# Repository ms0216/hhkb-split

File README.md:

# hhkb-split

**HHKB Professional HYBRID Type-S（PD-KB800WNS / US配列 / 無刻印）の使い勝手を、
完全分割型で再現する自作キーボード。**

> **開発中です。** 実機での動作確認はまだ済んでいません。
> 現状は「CAD とファームウェアがビルドを通り、寸法と配列が実機調査で裏付けられている」段階です。
> 3Dプリント・基板発注・組み立ては未実施。

## 基本方針

**HHKB オリジナルの使い勝手を極力踏襲する。** 分割にするために必要な変更だけを加え、
それ以外は変えない。この方針は [tools/test_invariants.py](tools/test_invariants.py) に
テストとして書き下してあり、設計の都合で妥協しようとすると機械的に落ちる。

守っているもの:

| 項目 | 値 | 根拠 |
|---|---|---|
| キーピッチ | 19.05mm | 実機公称 |
| 打鍵面の傾斜 | 7.3° | 実機ノギス実測 |
| 手前端の高さ | 17.5mm | 実測 17mm と別レビュー約18mm の中間 |
| キートップ高さ（各段） | 26.7 / 29.2 / 31.6 / 35.6 / 40.0mm | 公称全高 40mm から導出 |
| チルト脚 | 0 / 3 / 6° の3段階 | 実機と同一 |
| 行ずれ | HHKB と同一（格子配列にしない） | 実機 |
| 最下段 | 外側 1u / スペース寄り 1.5u | QMK info.json + KLE 図 |
| 電源 | 単3 × 2 | 実機と同じ思想（リポにしない） |

変更したもの:

- **打鍵感** — 静電容量無接点（Topre）→ MX 互換 + ホットスワップソケット
- **分割** — 6u スペースを 3u + 3u に分割。**左右とも Space**。キーは増やさない（60 → 61）
- **Mac/Win 切替** — 実機の DIP スイッチ相当をソフトウェアで実現
- **無線** — 左右間も Bluetooth。TRRS 有線は障害時の予備でしかない

## 構成

```
layout/        HHKB オリジナルと分割版のキー配列（JSON）
tools/         配列読み込み・CAD生成・検証（Python / build123d）
config/        ZMK ファームウェア設定
docs/hardware/ 実機の寸法調査と、その出典・失敗した調査経路の記録
build/         生成された STL（未印刷）
```

### tools/

パラメトリック CAD。`build123d`（OCCT）でモデルを生成し、`trimesh` で
メッシュ健全性を、OrcaSlicer CLI で実際にスライスできるかを検証する。

```bash
python -m pytest tools          # 全検査（約 14 分。件数は --collect-only で数える）
python tools/gen_case.py        # ケースを生成
python tools/verify.py          # メッシュとスライスの検証
```

[tools/interface.py](tools/interface.py) は**プレート・ケース・基板が共有する境界**を
1 箇所に集めたもの。ケースは刷り直せるが基板は発注し直すと高くつくので、
ここを凍結してから発注する。

### config/

ZMK。ボードは **Seeed Studio XIAO nRF52840**（技適 211-220207）。
XIAO は GPIO が 11 本しかなく普通のマトリクスに 1 本足りないため、列の駆動に
シフトレジスタ **SN74LVC595APWR** を使う（ZMK 公式が推奨する手段）。**74HC595 では打ち止め時に規格外**（動作電圧の下限 2.0V に対し、レールは 1.8V まで下がる）と分かって差し替えた。キーごとにダイオード 1 個の
ごく普通の行×列マトリクスなので、同時押しでゴーストが出ない。
当初はチャープレックス方式で設計していたが、基板発注前に破棄した
（[判断根拠](docs/hardware/decisions/2026-08-07-keyscan.md)）。

| シールド | 用途 |
|---|---|
| `hhkb_split_left` / `hhkb_split_right` | 本番。4レイヤー × 61キー |
| `proto_direct` | 疎通確認（XIAO 1個・キー2個）（[手順書](docs/hardware/task-c1-smoke-test.md)）✅ 実機確認済 |
| `proto_matrix` | マトリクス配線とゴースト試験の治具（[手順書](docs/hardware/task-c2-keyscan.md)）✅ 実機確認済 |

ビルドは GitHub Actions（ZMK 公式の再利用ワークフロー）。Actions の成果物から
`.uf2` をダウンロードして書き込む。

### 検証タスクの手順書

実機で確かめる作業は、配置図と判定基準つきの手順書にしてある。

| タスク | 内容 | 状態 |
|---|---|---|
| [C1](docs/hardware/task-c1-smoke-test.md) | 疎通確認（XIAO・書き込み・ZMK が実機で動くか） | ✅ 合格 |
| [C2](docs/hardware/task-c2-keyscan.md) | キースキャン（マトリクス・ゴースト・シフトレジスタ。治具は 74HC595、本番は 74LVC595） | ✅ C2-a 合格 / ⬜ C2-b |
| [C3](docs/hardware/task-c3-ble-split.md) | BLE 分割（左右同時押しが崩れないか） | ⬜ |
| [C4・C5](docs/hardware/task-c4-c5-power.md) | 乾電池給電・逆流の測定・電池残量 | ⬜ |
| [C6](docs/hardware/task-c6-confirm-on-real-hhkb.md) | 実機の DIP スイッチとキーマップを確認 | ⬜ **部品不要** |
| [B3](docs/hardware/task-b3-print-and-compare.md) | 3Dプリントして実機と比べる | ⬜ **部品不要** |

書き込みでつまずいたときは [xiao-flash-recovery.md](docs/hardware/xiao-flash-recovery.md)。

### docs/hardware/

実機を分解せず、公開情報だけから寸法を確定させた記録。
[reference-sources.md](docs/hardware/reference-sources.md) には**失敗した調査経路 11 件**も
残してある（例: PFU 公式記事に載っていた側面写真 4 枚が、よく見ると HHKB ではなく
MX 軸のキーボードだった）。同じ穴に落ちないため。

## 進捗

| フェーズ | 状態 |
|---|---|
| A. 実機寸法の確定 | ✅ 完了 |
| B. 機構設計（プレート・ケース） | ✅ STL 生成・検証済み / ⬜ 未印刷（[B3](docs/hardware/task-b3-print-and-compare.md)） |
| C. 電気・ファームウェア検証 | 🔶 進行中（**C1・C2-a 合格**。C2-b は 74HC595（治具用。本番は 74LVC595）待ち、C3〜C5 は部品待ち） |
| D. 基板設計（KiCad → JLCPCB） | 🔶 D1・D2a 完了（外形・キー配置・マトリクス）。[詳細](pcb/README.md) |
| E. 組み立て・実機調整 | ⬜ 未着手 |

## ライセンス

未定。

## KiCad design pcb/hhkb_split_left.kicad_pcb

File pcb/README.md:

# 基板（KiCad）

## 現在の状態

| 段階 | 内容 | 状態 |
|---|---|---|
| D1 | 外形・キー配置・取付穴 | ✅ 完了。DRC 違反 0 |
| D2a | マトリクス（61キー ＋ 61ダイオード ＋ 行列のネット） | ✅ 完了 |
| D3a | マトリクスの配線（行・列・スイッチ→ダイオード） | ✅ 左は違反 0 / ⚠️ 右に 5 件（下記） |
| D2b | XIAO・74HC595・電源の搭載 | ⬜ 3D 実装の検討が要る（下記） |
| D3 | 配線（行・列・電源） | ⬜ |
| D4 | JLCPCB 向け出力（ガーバー・BOM・CPL） | ⬜ |

マトリクスは配線済み（**未配線 0**）。左半分は DRC 違反 0。

### 右半分に残る 5 件

すべて `hole_clearance`（配線が穴に近すぎる）で、原因は特定済み。

列のバスは行間の空きを横に渡るが、**スタビライザーの穴がその帯に食い込んで
いる**（キー中心 +6.2〜10.2mm）。9 列ぶんの通り道を 0.8mm 間隔で並べると、
穴を避けきれない列が出る。

取りうる手:
  1. 穴に当たる区間だけ迂回させる（自動配線の作り込み）
  2. 配線幅と間隔を詰めて通り道を増やす（JLCPCB の最小は 0.127mm）
  3. 該当箇所だけ KiCad の GUI で手直しする

**左半分が完全に通っているので、方式の問題ではない。**

### D2b でまず決めること — XIAO をどこに置くか

XIAO は基板の**裏面**に付く（表に置くとキーキャップと当たる）。ところが
USB-C は実機と同じく**背面**に出す必要があり、基板の裏の背面側には
**電池室（幅 109mm）**が横断している。左半分では電池の外側に
15mm ほどしか残らず、XIAO の 17.8mm が入らない。

取りうる案:
  1. USB-C を基板端のコネクタとして別に載せ、XIAO は空いている隅に置く
  2. 電池を左右に振り分けて中央を空ける（ケースの作り直しが要る）
  3. USB の位置を実機と変える（使い勝手の方針に反するので最後）

**ケースの 3D モデルと合わせて検討する必要がある。** 実測（Task C4）で
電源部の構成が確定してから着手するのが順序として正しい。

## 生成のしかた

`pcbnew` は KiCad 同梱の Python にしか無いので、そちらで動かす。

```bash
/Applications/KiCad/KiCad.app/Contents/Frameworks/Python.framework/Versions/3.9/bin/python3.9 \
    tools/gen_pcb.py
```

## 検証のしかた

```bash
# デザインルール検査（違反があれば終了コードが非 0）
/Applications/KiCad/KiCad.app/Contents/MacOS/kicad-cli pcb drc \
    --severity-error --exit-code-violations pcb/hhkb_split_left.kicad_pcb

# 生成物が設計値と一致するか（通常の pytest から実行できる）
python -m pytest tools/test_pcb.py

# 目で見る
/Applications/KiCad/KiCad.app/Contents/MacOS/kicad-cli pcb render \
    --output /tmp/pcb.png --side top pcb/hhkb_split_left.kicad_pcb
```

`.kicad_pcb` はテキスト（S 式）なので、`tools/test_pcb.py` は pcbnew 無しで
読める。**生成した基板を読み返して、プレート・ケースと突き合わせる**のが要点。
別々に生成される以上、同じ設計値から導いていても座標変換を間違えれば静かに
ずれる。ずれたまま発注すると数万円が無駄になる。

## 寸法

| | 左 | 右 |
|---|---|---|
| 基板 | 140.36 × 102.00mm | 173.70 × 102.00mm |
| スイッチ | 27 | 34 |
| スタビライザー | 2 | 2 |
| 取付穴 | 7 | 7 |

外形はプレートより片側 3.0mm 小さい（`interface.PCB_INSET`）。ケースの
側壁 2.4mm の内側に収める必要があるため。

奥行 102.00mm ＝ プレート 108.00mm − 6.0mm。プレートの 108.00mm は
HHKB 実機の本体奥行そのもの。

## ライブラリ

`lib/` を参照。KiCad 標準に無い 3.00u とホットスワップソケットだけを
kiswitch から取り込み、寸法を規格値と照合してある。

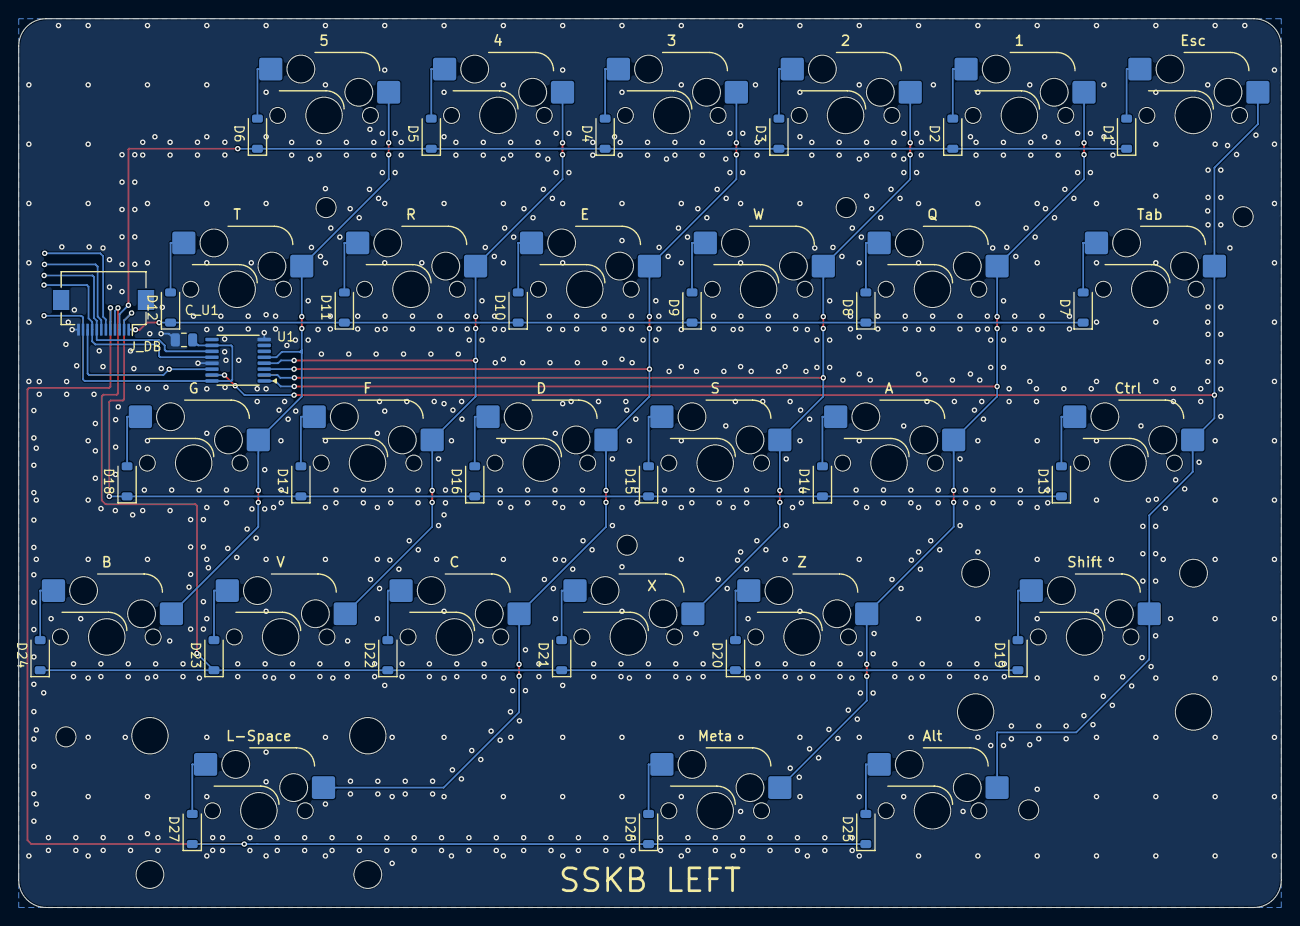
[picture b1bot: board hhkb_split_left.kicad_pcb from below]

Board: 2 copper layers, 138.4 x 97.4 mm, 65 parts (30 on the bottom side), 43 nets.

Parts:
C_U1: 100nF; C_0805_2012Metric
D1, D2, D3, D4, D5, D6, D7, D8, D9, D10, D11, D12, D13, D14, D15, D16, D17, D18, D19, D20, D21, D22, D23, D24, D25, D26, D27: BAT46W; D_SOD-123
H0, H1, H2, H3, H4, H5: MountingHole_2.2mm_M2
J_DB: FH12-12S-0.5SH(55); Hirose_FH12-12S-0.5SH_1x12-1MP_P0.50mm_Horizontal
ST19, ST27: Stabilizer_Cherry_MX_2.00u
SW1, SW2, SW3, SW4, SW5, SW6, SW8, SW9, SW10, SW11, SW12, SW14, SW15, SW16, SW17, SW18, SW20, SW21, SW22, SW23, SW24, SW25: CPG151101S11-2; SW_Hotswap_Kailh_MX_1.00u
SW7, SW26: CPG151101S11-2; SW_Hotswap_Kailh_MX_1.50u
SW13: CPG151101S11-2; SW_Hotswap_Kailh_MX_1.75u
SW19: CPG151101S11-2; SW_Hotswap_Kailh_MX_2.25u
SW27: CPG151101S11-2; SW_Hotswap_Kailh_MX_2.75u
U1: 74LVC595; TSSOP-16_4.4x5mm_P0.65mm

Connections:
COL0: SW1.1, SW7.1, SW13.1, SW19.1, SW25.1, U1.15
COL1: SW2.1, SW8.1, SW14.1, SW20.1, SW26.1, U1.1
COL2: SW3.1, SW9.1, SW15.1, SW21.1, U1.2
COL3: SW4.1, SW10.1, SW16.1, SW22.1, SW27.1, U1.3
COL4: SW5.1, SW11.1, SW17.1, SW23.1, U1.4
COL5: SW6.1, SW12.1, SW18.1, SW24.1, U1.5
CS: J_DB.9, U1.12
GND: C_U1.2, J_DB.12, U1.8, U1.13
ROW_A: D25.1, D26.1, D27.1, J_DB.5
ROW_B: D19.1, D20.1, D21.1, D22.1, D23.1, D24.1, J_DB.4
ROW_C: D1.1, D2.1, D3.1, D4.1, D5.1, D6.1, J_DB.3
ROW_D: D13.1, D14.1, D15.1, D16.1, D17.1, D18.1, J_DB.2
ROW_E: D7.1, D8.1, D9.1, D10.1, D11.1, D12.1, J_DB.1
SPI_MOSI: J_DB.10, U1.14
SPI_SCK: J_DB.8, U1.11
SW1_D: D1.2, SW1.2
SW2_D: D2.2, SW2.2
SW3_D: D3.2, SW3.2
SW4_D: D4.2, SW4.2
SW5_D: D5.2, SW5.2
SW6_D: D6.2, SW6.2
SW7_D: D7.2, SW7.2
SW8_D: D8.2, SW8.2
SW9_D: D9.2, SW9.2
SW10_D: D10.2, SW10.2
SW11_D: D11.2, SW11.2
SW12_D: D12.2, SW12.2
SW13_D: D13.2, SW13.2
SW14_D: D14.2, SW14.2
SW15_D: D15.2, SW15.2
SW16_D: D16.2, SW16.2
SW17_D: D17.2, SW17.2
SW18_D: D18.2, SW18.2
SW19_D: D19.2, SW19.2
SW20_D: D20.2, SW20.2
SW21_D: D21.2, SW21.2
SW22_D: D22.2, SW22.2
SW23_D: D23.2, SW23.2
SW24_D: D24.2, SW24.2
SW25_D: D25.2, SW25.2
SW26_D: D26.2, SW26.2
SW27_D: D27.2, SW27.2
V3V3: C_U1.1, J_DB.11, U1.10, U1.16

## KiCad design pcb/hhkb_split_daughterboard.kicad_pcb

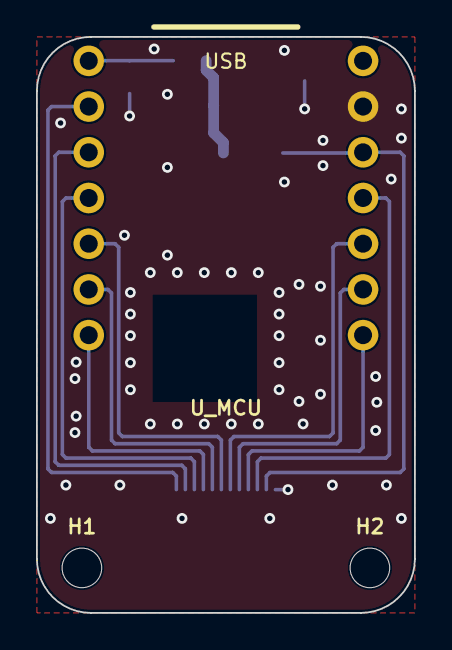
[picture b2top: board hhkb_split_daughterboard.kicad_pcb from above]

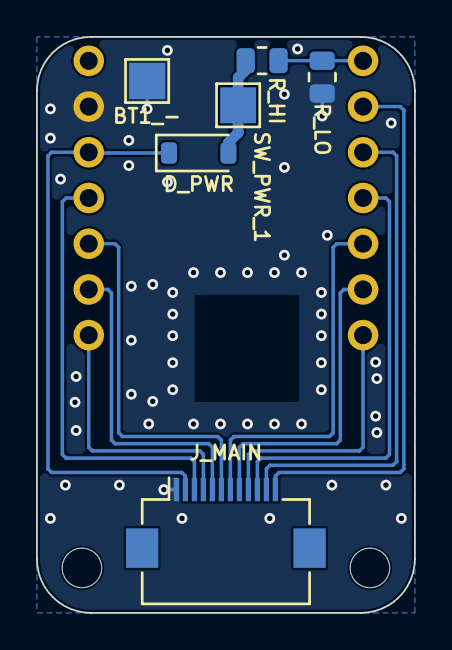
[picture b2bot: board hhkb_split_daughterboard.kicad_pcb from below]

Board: 2 copper layers, 21.0 x 32.0 mm, 9 parts (6 on the bottom side), 14 nets.

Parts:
BT1_-: battery_holder; TestPoint_Pad_2.0x2.0mm
D_PWR: B5819W; D_SOD-123
H1, H2: MountingHole_2.2mm_M2
J_MAIN: FFC 12P 0.5mm; Hirose_FH12-12S-0.5SH_1x12-1MP_P0.50mm_Horizontal
R_HI: 1M; R_0805_2012Metric
R_LO: 1M; R_0805_2012Metric
SW_PWR_1: wire_pads; TestPoint_Pad_2.0x2.0mm
U_MCU: XIAO nRF52840; XIAO_nRF52840

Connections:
CS: J_MAIN.4, U_MCU.D7
GND: BT1_-.1, J_MAIN.1, R_LO.2, U_MCU.GND
ROW_A: J_MAIN.8, U_MCU.D5
ROW_B: J_MAIN.9, U_MCU.D6
ROW_C: J_MAIN.10, U_MCU.D3
ROW_D: J_MAIN.11, U_MCU.D2
ROW_E: J_MAIN.12, U_MCU.D1
SPARE: J_MAIN.7, U_MCU.D4
SPARE2: J_MAIN.6, U_MCU.D9
SPI_MOSI: J_MAIN.3, U_MCU.D10
SPI_SCK: J_MAIN.5, U_MCU.D8
V3V3: D_PWR.1, J_MAIN.2, U_MCU.3V3
VBATT_SENSE: R_HI.2, R_LO.1, U_MCU.D0
VBATT_SW: D_PWR.2, R_HI.1, SW_PWR_1.1

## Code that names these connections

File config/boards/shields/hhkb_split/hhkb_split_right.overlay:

/*
 * 右半分（34 キー）。分割の周辺側（ペリフェラル）。
 *
 * 列は 9 本。595（SN74LVC595A）は 8 出力なので 2 個を数珠つなぎにして出力 0..8 を使う
 * （ngpios = 16）。最上段が 9 キーあるため。
 * 右半分の基板上では列 0..7 だが、キーマップ全体では列 6..13 に当たるので、
 * col-offset で 6 だけずらす。これが ZMK の分割の標準的な書き方。
 */
#include "hhkb_split.dtsi"

&default_transform {
	col-offset = <6>;
};

/* 右だけ 595 を 2 個つなぐ。数珠つなぎのぶん取りこぼしやすくなるので、
 * 速い打鍵での確認を Task C2-b の重点項目にしている。 */
&shifter {
	ngpios = <16>;
};

&kscan0 {
	col-gpios
		= <&shifter 0 GPIO_ACTIVE_HIGH>
		, <&shifter 1 GPIO_ACTIVE_HIGH>
		, <&shifter 2 GPIO_ACTIVE_HIGH>
		, <&shifter 3 GPIO_ACTIVE_HIGH>
		, <&shifter 4 GPIO_ACTIVE_HIGH>
		, <&shifter 5 GPIO_ACTIVE_HIGH>
		, <&shifter 6 GPIO_ACTIVE_HIGH>
		, <&shifter 7 GPIO_ACTIVE_HIGH>
		, <&shifter 8 GPIO_ACTIVE_HIGH>
		;
};

	/*
	 * **J_DB から遠い行ほど、パッド列の外側(12番寄り)へ。**
	 * （2026-08-15・利用者の指摘で組み直した）。考え方は左基板と同じ。
	 *
	 * ⚠️ **2026-08-17 に組み直した。**それまでこの並びは**左基板と同一**で、
	 * 「逆になる」と書いておきながら実装が追随していなかった。
	 *
	 * **効く順序は「パッドの外側ほど遠い行」。**J_DB のパッド列は扇の
	 * 根元で、**外側(12番)を通る芯線が遠い行へ、内側(8番)が近い行へ**
	 * 行くと交差しない。パッドの x そのものではなく、**束の中でどれだけ
	 * 外を通るか**が効く（利用者の指摘。ROW_E(#12) は最も遠くて長い
	 * のが正しい姿で、302mm あってよい）。
	 *
	 * 行バスの y は左右で同じ（行0 62.25 … 行4 138.45）。J_DB の y は
	 * 85.375 なので、**コネクタからの距離**は
	 *   行1(81.3) 4.1 < 行2(100.35) 15.0 < 行0(62.25) 23.1
	 *   < 行3(119.4) 34.0 < 行4(138.45) 53.1
	 * 近い行から順に、内側のパッド(8→12)へ割り当てる:
	 *   行1=ROW_A(#8) / 行2=ROW_B(#9) / 行0=ROW_C(#10)
	 *   / 行3=ROW_D(#11) / 行4=ROW_E(#12)
	 *
	 * 行番号 → GPIO は ROW_LANES(D5=A/D6=B/D3=C/D2=D/D1=E) の逆引き:
	 *   行0=ROW_C=D3 / 行1=ROW_A=D5 / 行2=ROW_B=D6
	 *   / 行3=ROW_D=D2 / 行4=ROW_E=D1
	 *
	 * ⚠️ **左基板とは違う並びになる。**揃えようとしないこと。
	 * ⚠️ **ネット名(#8=ROW_A…#12=ROW_E)は左右で同じ。**動かすのは
	 * 「どのレーンがどの行に載るか」だけ（circuit.py の J_DB は共通）。
	 *
	 * ⚠️ **この向きにすると未配線が 2 本残る**（組み直す前は 0 本）。
	 * **数字が悪いほうが正しい。**前の並びは未配線 0 だったが、扇が
	 * 交差したまま通っていただけで、ROW_A が最遠の行まで斜めに降りて
	 * いた。**未配線 0 を根拠にこの並びへ戻さないこと。**
	 * 残り 2 本は ROW_D(J_DB #11 → 行3) と GND(C_U2 のパッド 2 →
	 * ベタ)。後者は ROW とは無関係で、C_U2 の位置の件。
	 */
&kscan0 {
	row-gpios
		= <&xiao_d 3 (GPIO_ACTIVE_HIGH | GPIO_PULL_DOWN)>
		, <&xiao_d 5 (GPIO_ACTIVE_HIGH | GPIO_PULL_DOWN)>
		, <&xiao_d 6 (GPIO_ACTIVE_HIGH | GPIO_PULL_DOWN)>
		, <&xiao_d 2 (GPIO_ACTIVE_HIGH | GPIO_PULL_DOWN)>
		, <&xiao_d 1 (GPIO_ACTIVE_HIGH | GPIO_PULL_DOWN)>
		;
};
